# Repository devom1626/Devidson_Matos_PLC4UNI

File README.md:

# Devidson\_Matos\_PLC4UNI

CONSISTE EN EL "MAKING OF" DE UNA TARJETA TERMINADA DE PLC USANDO EL FAMOSO ESP32 COMO CEREBRO PRINCIPAL, APLICANDO FUNCIONES GENERALES DE UN PLC DE USO DEL DIA A DIA.

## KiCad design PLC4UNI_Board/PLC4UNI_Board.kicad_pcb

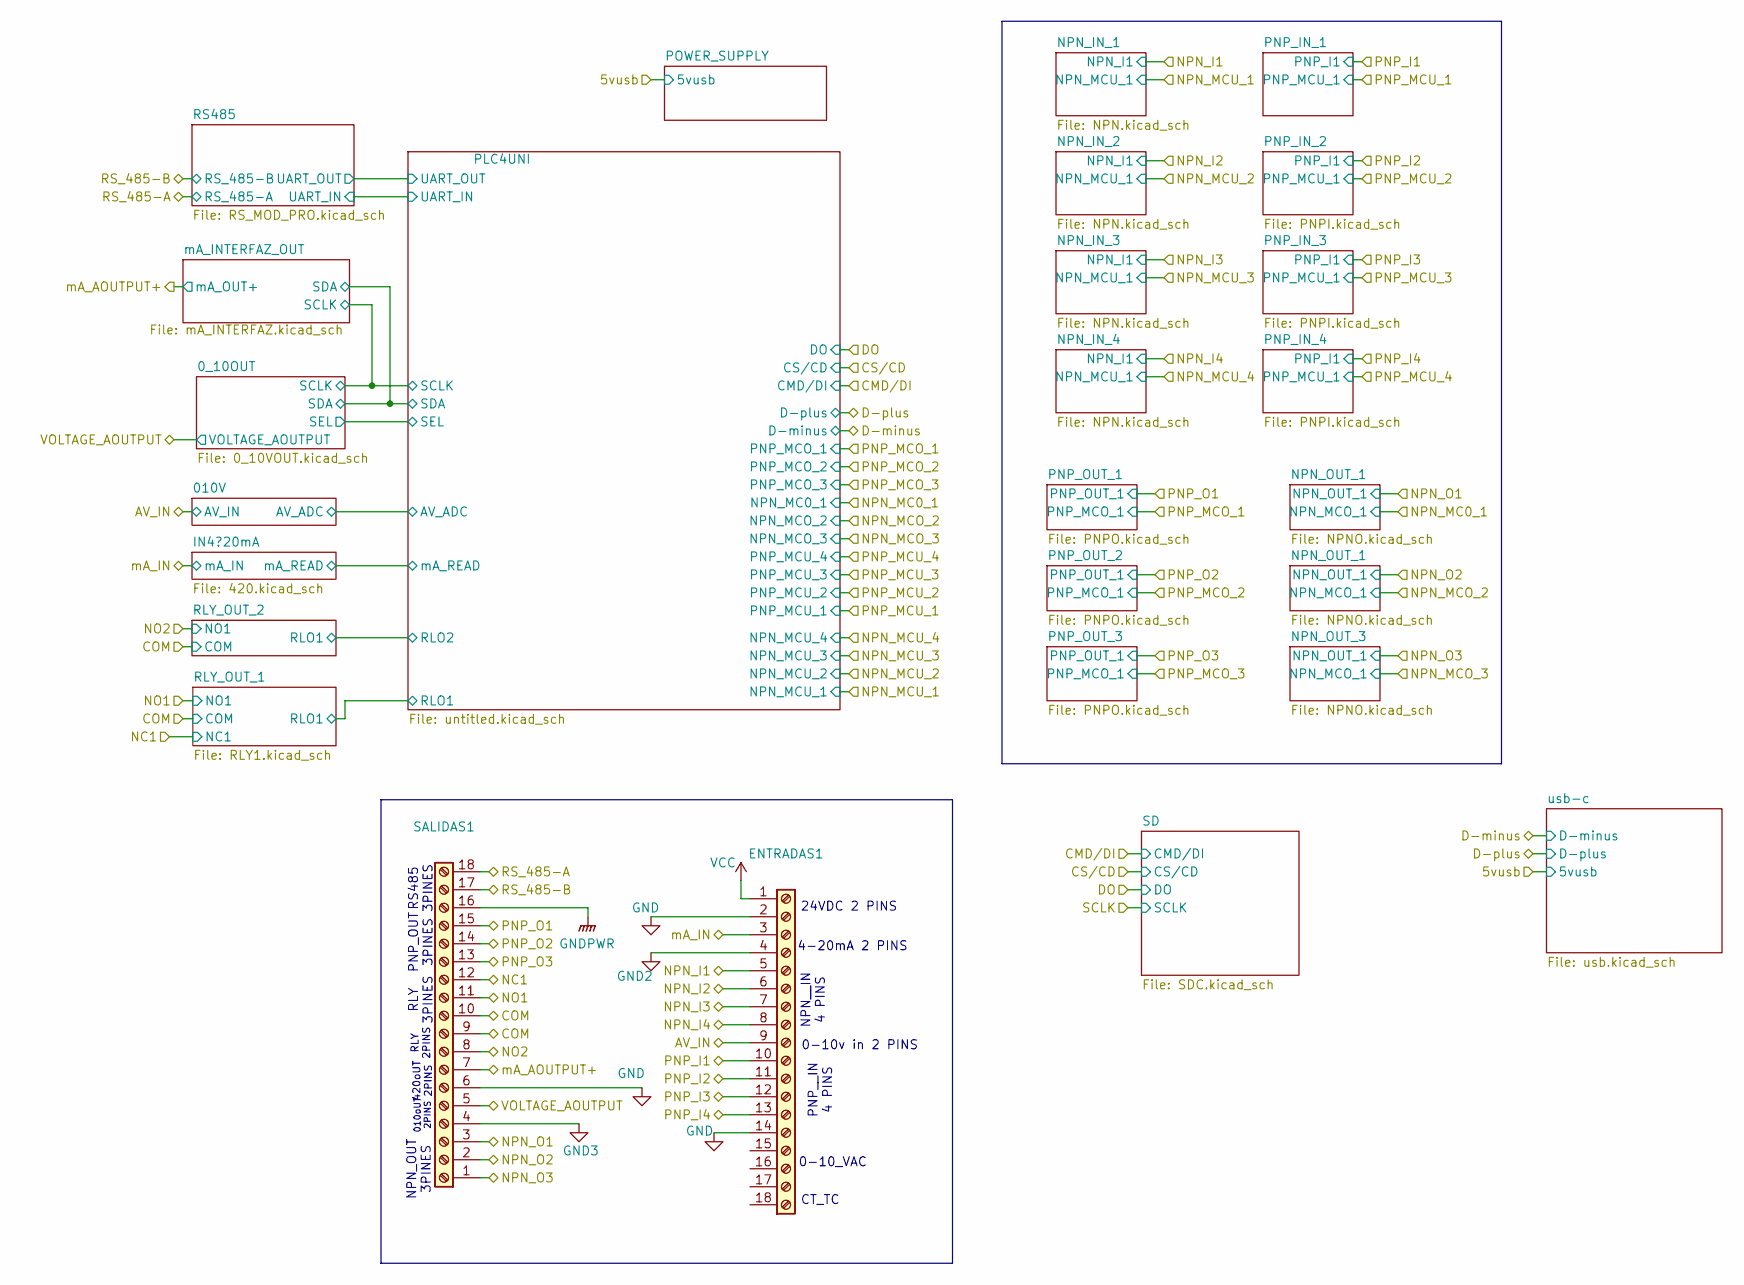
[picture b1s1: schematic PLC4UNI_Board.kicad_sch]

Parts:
ENTRADAS1: Screw_Terminal_01x18; TerminalBlock_MaiXu_MX126-5.0-18P_1x18_P5.00mm
SALIDAS1: Screw_Terminal_01x18; TerminalBlock_MaiXu_MX126-5.0-18P_1x18_P5.00mm

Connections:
/AV_IN: ENTRADAS1.9 (Pin_10); also elsewhere on the board
/COM: SALIDAS1.9, SALIDAS1.10; also elsewhere on the board
/NC1: SALIDAS1.12 (7); also elsewhere on the board
/NO1: SALIDAS1.11; also elsewhere on the board
/NO2: SALIDAS1.8; also elsewhere on the board
/NPN_I1: ENTRADAS1.5 (Pin_14); also elsewhere on the board
/NPN_I2: ENTRADAS1.6 (Pin_13); also elsewhere on the board
/NPN_I3: ENTRADAS1.7 (Pin_12); also elsewhere on the board
/NPN_I4: ENTRADAS1.8 (Pin_11); also elsewhere on the board
/NPN_O1: SALIDAS1.3; also elsewhere on the board
/NPN_O2: SALIDAS1.2; also elsewhere on the board
/NPN_O3: SALIDAS1.1; also elsewhere on the board
/PNP_I1: ENTRADAS1.10 (Pin_9); also elsewhere on the board
/PNP_I2: ENTRADAS1.11 (Pin_8); also elsewhere on the board
/PNP_I3: ENTRADAS1.12 (Pin_7); also elsewhere on the board
/PNP_I4: ENTRADAS1.13 (Pin_6); also elsewhere on the board
/PNP_O1: SALIDAS1.15; also elsewhere on the board
/PNP_O2: SALIDAS1.14; also elsewhere on the board
/PNP_O3: SALIDAS1.13; also elsewhere on the board
/RS_485-A: SALIDAS1.18; also elsewhere on the board
/RS_485-B: SALIDAS1.17; also elsewhere on the board
/VOLTAGE_AOUTPUT: SALIDAS1.5; also elsewhere on the board
/mA_AOUTPUT+: SALIDAS1.7; also elsewhere on the board
/mA_IN: ENTRADAS1.3 (Pin_16); also elsewhere on the board
GND: ENTRADAS1.2 (Pin_17), ENTRADAS1.14 (Pin_5), SALIDAS1.6; also elsewhere on the board
GND2: ENTRADAS1.4 (Pin_15); also elsewhere on the board
GND3: SALIDAS1.4; also elsewhere on the board
GNDPWR: SALIDAS1.16; also elsewhere on the board
VCC: ENTRADAS1.1 (Pin_18); also elsewhere on the board

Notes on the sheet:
4-20mA 2 PINS
0-10_VAC
NPN_OUT 3PINES
010oUT 2PINS
0-10v in 2 PINS
PNP_OUT 3PINES
CT_TC
PNP__IN 4 PINS
RS485 3PINES
NPN__IN 4 PINS
RLY 2PINS
RLY 3PINES
24VDC 2 PINS
420oUT 2PINS

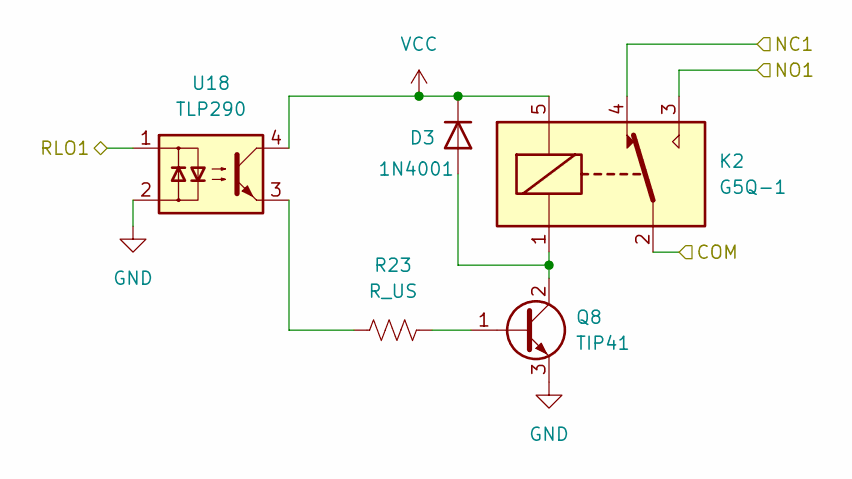
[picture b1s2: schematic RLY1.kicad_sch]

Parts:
D3: 1N4001; D_DO-41_SOD81_P10.16mm_Horizontal
K2: G5Q-1; Relay_SPDT_Omron-G5Q-1
Q8: TIP41; TO-252-2
R23: R_US; R_0201_0603Metric
U18: TLP290; SOP-4_4.4x2.6mm_P1.27mm

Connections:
/COM: K2.2; also elsewhere on the board
/NO2: K2.3; also elsewhere on the board
/PLC4UNI/RLO2: U18.1; also elsewhere on the board
/RLY_OUT_2/NC1: K2.4
GND: Q8.3 (E), U18.2; also elsewhere on the board
unnamed: D3.2 (A), K2.1, Q8.2 (C)
unnamed: Q8.1 (B), R23.2
unnamed: R23.1, U18.3
VCC: D3.1 (K), K2.5, U18.4; also elsewhere on the board

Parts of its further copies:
D1: 1N4001; D_DO-41_SOD81_P10.16mm_Horizontal
K1: G5Q-1; Relay_SPDT_Omron-G5Q-1
Q7: TIP41; TO-252-2
R22: R_US; R_0201_0603Metric
U17: TLP290; SOP-4_4.4x2.6mm_P1.27mm

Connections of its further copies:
/COM: K1.2; also elsewhere on the board
/NC1: K1.4; also elsewhere on the board
/NO1: K1.3; also elsewhere on the board
/PLC4UNI/RLO1: U17.1; also elsewhere on the board
GND: Q7.3 (E), U17.2; also elsewhere on the board
unnamed: D1.2 (A), K1.1, Q7.2 (C)
unnamed: Q7.1 (B), R22.2
unnamed: R22.1, U17.3
VCC: D1.1 (K), K1.5, U17.4; also elsewhere on the board

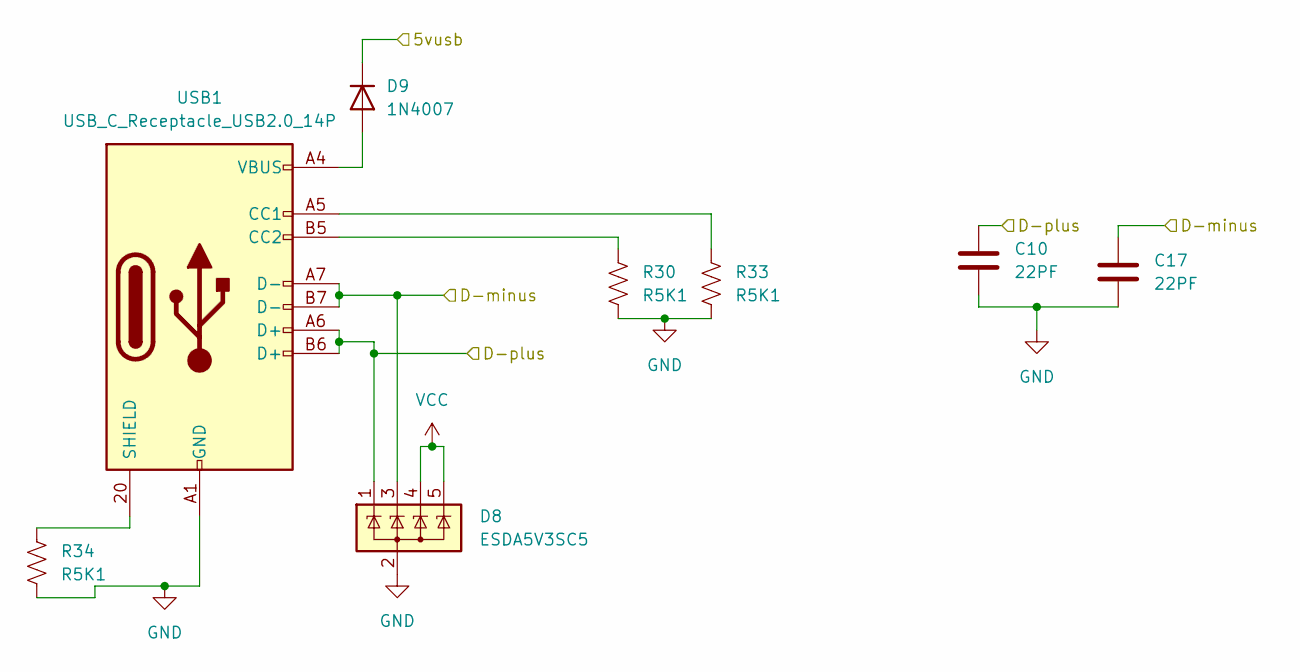
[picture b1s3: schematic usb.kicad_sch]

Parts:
C10, C17: 22PF; C_0603_1608Metric
D8: ESDA5V3SC5; SOT-23-5
D9: 1N4007; D_0603_1608Metric_Pad1.05x0.95mm_HandSolder
R30, R33, R34: R5K1; R_0201_0603Metric
USB1: USB_C_Receptacle_USB2.0_14P; USB-C-TH_HX-TYPE-C-16P-180-LC-BH10.0-TYPE-C-VERTICAL

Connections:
/5vusb: D9.1 (K); also elsewhere on the board
/D-minus: C17.1, D8.3 (K), USB1.A7 (D-), USB1.B7 (D-); also elsewhere on the board
/D-plus: C10.1, D8.1 (K), USB1.A6 (D+), USB1.B6 (D+); also elsewhere on the board
GND: C10.2, C17.2, D8.2 (A), R30.2, R33.2, R34.2, USB1.A1 (GND), USB1.A12 (GND), USB1.B1 (GND), USB1.B12 (GND); also elsewhere on the board
unnamed: D9.2 (A), USB1.A4 (VBUS), USB1.A9 (VBUS), USB1.B4 (VBUS), USB1.B9 (VBUS)
unnamed: R33.1, USB1.A5 (CC1)
unnamed: R30.1, USB1.B5 (CC2)
unnamed: R34.1, USB1.20 (SHIELD)
VCC: D8.4 (K), D8.5 (K); also elsewhere on the board

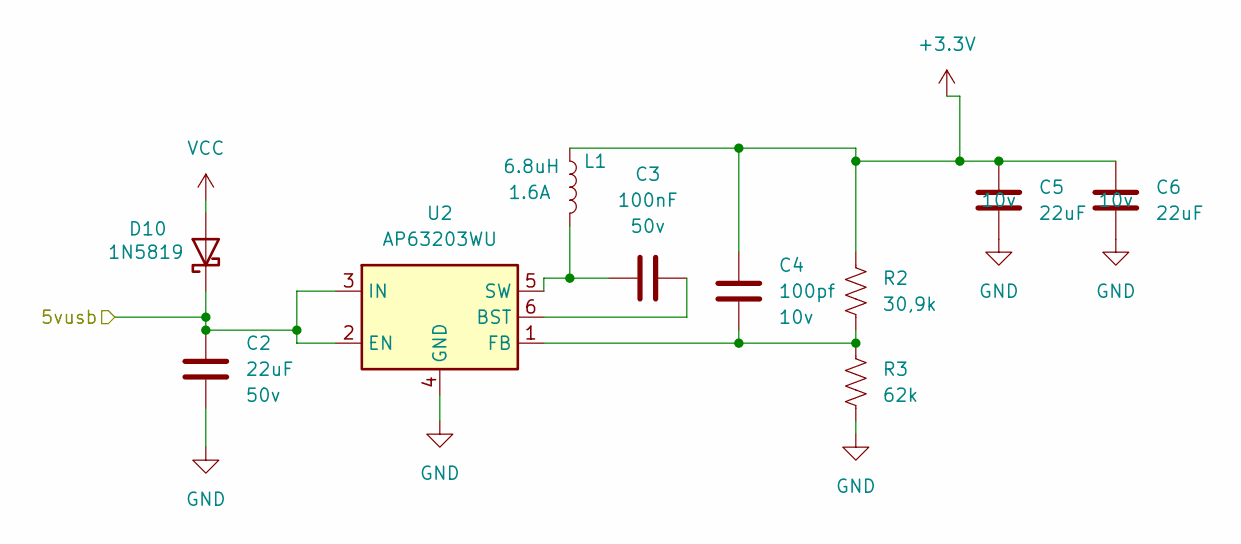
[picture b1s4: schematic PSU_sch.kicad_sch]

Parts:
C2: 22uF; C_1206_3216Metric
C3: 100nF; R_0805_2012Metric
C4: 100pf; R_0805_2012Metric
C5, C6: 22uF; C_0805_2012Metric_Pad1.18x1.45mm_HandSolder
D10: 1N5819; D_0603_1608Metric_Pad1.05x0.95mm_HandSolder
L1: 6.8uH_1.0A_4018; L_Changjiang_FNR5040S; Part Number NRS4018T6R8MDGJ; JLCPCB ID C223055
R2: 30,9k; R_0805_2012Metric
R3: 62k; R_0201_0603Metric
U2: AP63203WU; TSOT-23-6

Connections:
+3.3V: C4.1, C5.1, C6.1, L1.1, R2.1; also elsewhere on the board
/5vusb: C2.1, D10.1 (K), U2.2 (EN), U2.3 (IN); also elsewhere on the board
GND: C2.2, C5.2, C6.2, R3.2, U2.4 (GND); also elsewhere on the board
unnamed: C3.2, U2.6 (BST)
unnamed: C4.2, R2.2, R3.1, U2.1 (FB)
unnamed: C3.1, L1.2, U2.5 (SW)
VCC: D10.2 (A); also elsewhere on the board

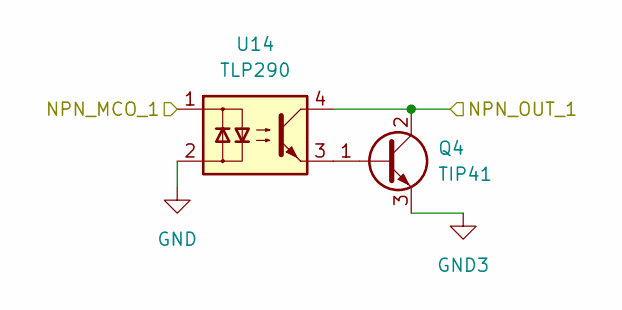
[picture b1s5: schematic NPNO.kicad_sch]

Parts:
Q4: TIP41; TO-252-2
U14: TLP290; SOP-4_4.4x2.6mm_P1.27mm

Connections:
/NPN_MCO_2: U14.1; also elsewhere on the board
/NPN_O2: Q4.2 (C), U14.4; also elsewhere on the board
GND: U14.2; also elsewhere on the board
GND3: Q4.3 (E); also elsewhere on the board
unnamed: Q4.1 (B), U14.3

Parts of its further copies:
Q5, Q6: TIP41; TO-252-2
U15, U16: TLP290; SOP-4_4.4x2.6mm_P1.27mm

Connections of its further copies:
/NPN_MC0_1: U16.1; also elsewhere on the board
/NPN_MCO_3: U15.1; also elsewhere on the board
/NPN_O1: Q6.2 (C), U16.4; also elsewhere on the board
/NPN_O3: Q5.2 (C), U15.4; also elsewhere on the board
GND: U15.2, U16.2; also elsewhere on the board
GND3: Q5.3 (E), Q6.3 (E); also elsewhere on the board
unnamed: Q5.1 (B), U15.3
unnamed: Q6.1 (B), U16.3

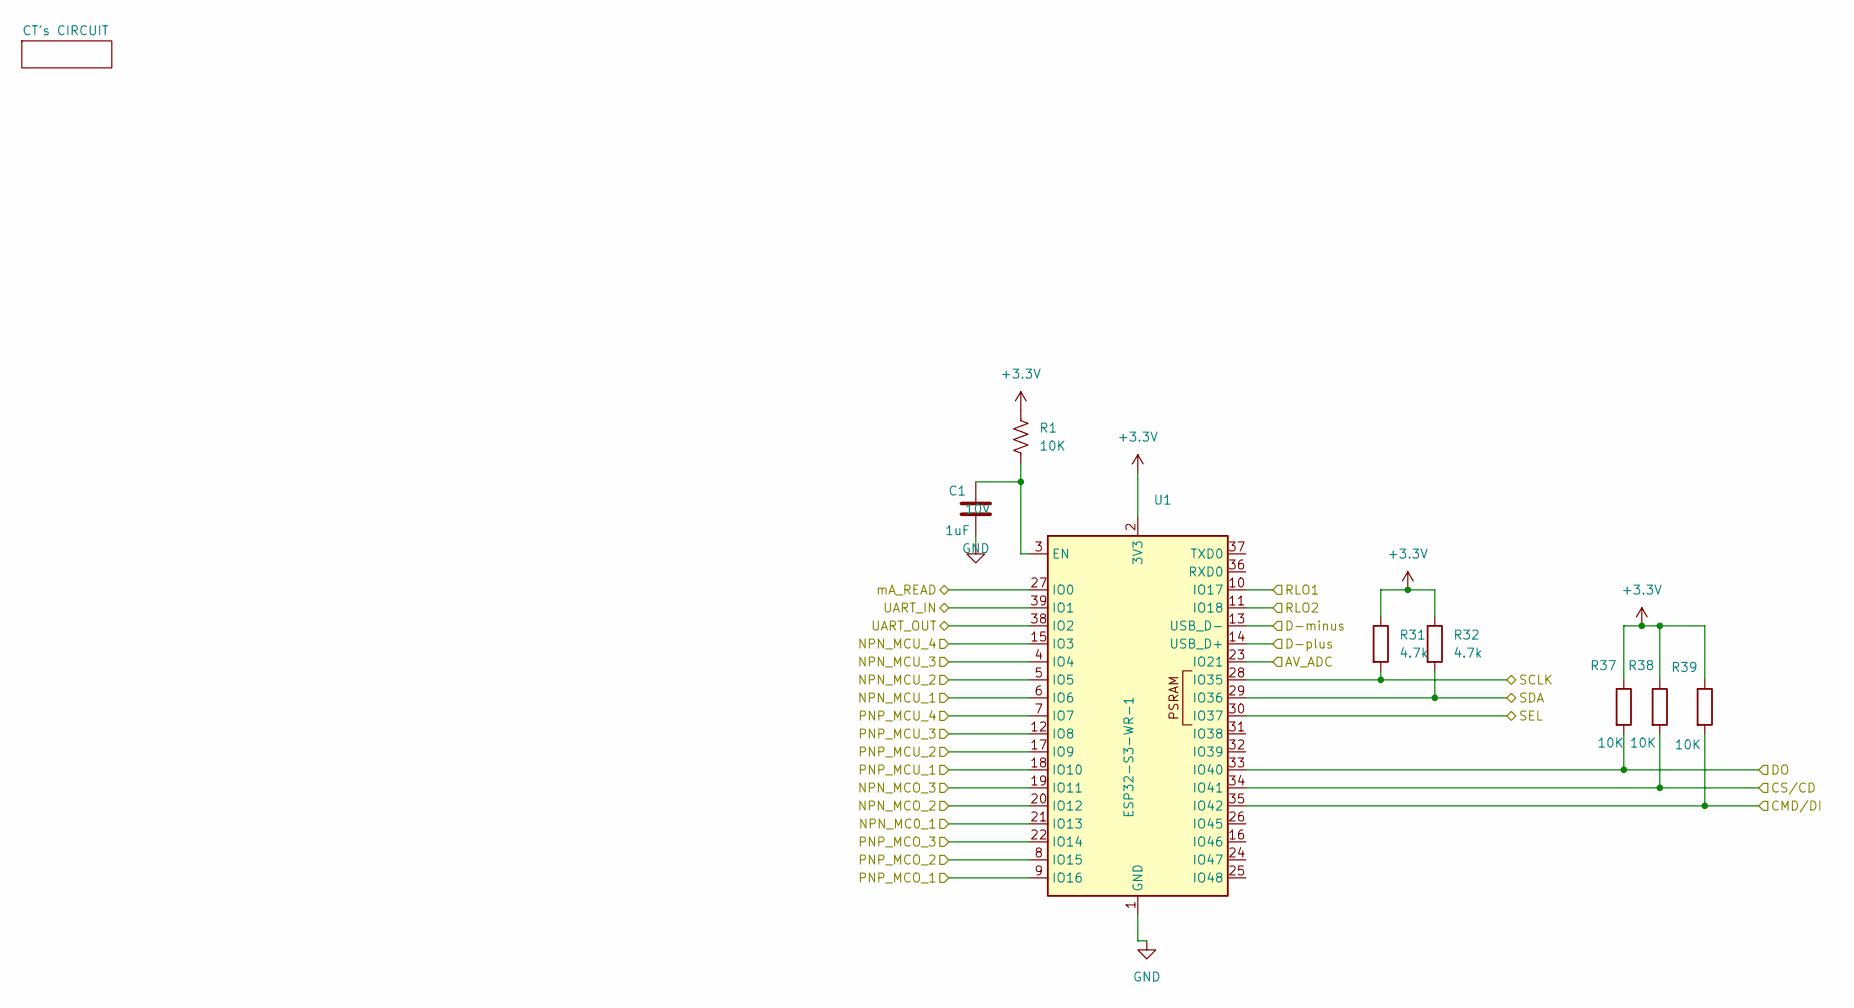
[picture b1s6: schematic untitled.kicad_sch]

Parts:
C1: 1uF; C_1206_3216Metric_Pad1.33x1.80mm_HandSolder
R1: 10K; R_0201_0603Metric
R31, R32: 4.7k; R_0603_1608Metric
R37, R38, R39: 10K; R_0603_1608Metric
U1: ESP32-S3-WR-1; ESP32-S3-WROOM-1

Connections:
+3.3V: R1.1, R31.1, R32.1, R37.1, R38.1, R39.1, U1.2 (3V3); also elsewhere on the board
/0_10OUT/SCLK: R31.2, U1.28 (IO35); also elsewhere on the board
/0_10OUT/SDA: R32.2, U1.29 (IO36); also elsewhere on the board
/0_10OUT/SEL: U1.30 (IO37); also elsewhere on the board
/010V/AV_ADC: U1.23 (IO21); also elsewhere on the board
/CMD/DI: R39.2, U1.35 (IO42); also elsewhere on the board
/CS/CD: R38.2, U1.34 (IO41); also elsewhere on the board
/D-minus: U1.13 (USB_D-); also elsewhere on the board
/D-plus: U1.14 (USB_D+); also elsewhere on the board
/DO: R37.2, U1.33 (IO40); also elsewhere on the board
/NPN_MC0_1: U1.21 (IO13); also elsewhere on the board
/NPN_MCO_2: U1.20 (IO12); also elsewhere on the board
/NPN_MCO_3: U1.19 (IO11); also elsewhere on the board
/NPN_MCU_1: U1.6 (IO6); also elsewhere on the board
/NPN_MCU_2: U1.5 (IO5); also elsewhere on the board
/NPN_MCU_3: U1.4 (IO4); also elsewhere on the board
/NPN_MCU_4: U1.15 (IO3); also elsewhere on the board
/PLC4UNI/RLO1: U1.10 (IO17); also elsewhere on the board
/PLC4UNI/RLO2: U1.11 (IO18); also elsewhere on the board
/PLC4UNI/UART_IN: U1.39 (IO1); also elsewhere on the board
/PLC4UNI/UART_OUT: U1.38 (IO2); also elsewhere on the board
/PNP_MCO_1: U1.9 (IO16); also elsewhere on the board
/PNP_MCO_2: U1.8 (IO15); also elsewhere on the board
/PNP_MCO_3: U1.22 (IO14); also elsewhere on the board
/PNP_MCU_1: U1.18 (IO10); also elsewhere on the board
/PNP_MCU_2: U1.17 (IO9); also elsewhere on the board
/PNP_MCU_3: U1.12 (IO8); also elsewhere on the board
/PNP_MCU_4: U1.7 (IO7); also elsewhere on the board
/mA_IN: U1.27 (IO0); also elsewhere on the board
GND: C1.2, U1.1 (GND), U1.40 (GND), U1.41 (GND); also elsewhere on the board
unnamed: C1.1, R1.2, U1.3 (EN)

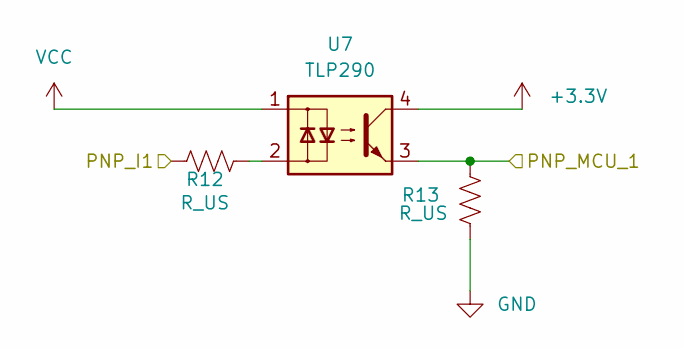
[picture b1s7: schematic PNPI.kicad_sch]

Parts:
R12: R_US; R_0603_1608Metric
R13: R_US; R_0201_0603Metric
U7: TLP290; SOP-4_4.4x2.6mm_P1.27mm

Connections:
+3.3V: U7.4; also elsewhere on the board
/PNP_I1: R12.1; also elsewhere on the board
/PNP_MCU_1: R13.1, U7.3; also elsewhere on the board
GND: R13.2; also elsewhere on the board
unnamed: R12.2, U7.2
VCC: U7.1; also elsewhere on the board

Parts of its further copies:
R14, R16, R18: R_US; R_0603_1608Metric
R15, R17, R19: R_US; R_0201_0603Metric
U8, U9, U10: TLP290; SOP-4_4.4x2.6mm_P1.27mm

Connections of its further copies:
+3.3V: U8.4, U9.4, U10.4; also elsewhere on the board
/PNP_I2: R14.1; also elsewhere on the board
/PNP_I3: R16.1; also elsewhere on the board
/PNP_I4: R18.1; also elsewhere on the board
/PNP_MCU_2: R15.1, U8.3; also elsewhere on the board
/PNP_MCU_3: R17.1, U9.3; also elsewhere on the board
/PNP_MCU_4: R19.1, U10.3; also elsewhere on the board
GND: R15.2, R17.2, R19.2; also elsewhere on the board
unnamed: R14.2, U8.2
unnamed: R16.2, U9.2
unnamed: R18.2, U10.2
VCC: U8.1, U9.1, U10.1; also elsewhere on the board

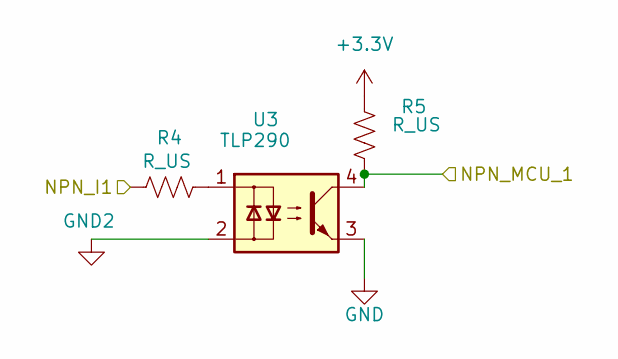
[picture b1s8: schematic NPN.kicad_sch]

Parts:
R4, R5: R_US; R_0201_0603Metric
U3: TLP290; SOP-4_4.4x2.6mm_P1.27mm

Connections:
+3.3V: R5.1; also elsewhere on the board
/NPN_I1: R4.1; also elsewhere on the board
/NPN_MCU_1: R5.2, U3.4; also elsewhere on the board
GND: U3.3; also elsewhere on the board
GND2: U3.2; also elsewhere on the board
unnamed: R4.2, U3.1

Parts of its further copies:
R6, R7, R8, R9, R10, R11: R_US; R_0201_0603Metric
U4, U5, U6: TLP290; SOP-4_4.4x2.6mm_P1.27mm

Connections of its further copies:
+3.3V: R7.1, R9.1, R11.1; also elsewhere on the board
/NPN_I2: R6.1; also elsewhere on the board
/NPN_I3: R8.1; also elsewhere on the board
/NPN_I4: R10.1; also elsewhere on the board
/NPN_MCU_2: R7.2, U4.4; also elsewhere on the board
/NPN_MCU_3: R9.2, U5.4; also elsewhere on the board
/NPN_MCU_4: R11.2, U6.4; also elsewhere on the board
GND: U4.3, U5.3, U6.3; also elsewhere on the board
GND2: U4.2, U5.2, U6.2; also elsewhere on the board
unnamed: R6.2, U4.1
unnamed: R8.2, U5.1
unnamed: R10.2, U6.1

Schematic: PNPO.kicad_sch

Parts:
Q9: TIP42; TO-252-2
U11: TLP290; SOP-4_4.4x2.6mm_P1.27mm

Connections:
/PNP_MCO_2: U11.1; also elsewhere on the board
/PNP_O2: Q9.2 (C), U11.4; also elsewhere on the board
GND: U11.2; also elsewhere on the board
unnamed: Q9.1 (B), U11.3
VCC: Q9.3 (E); also elsewhere on the board

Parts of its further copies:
Q10, Q11: TIP42; TO-252-2
U12, U13: TLP290; SOP-4_4.4x2.6mm_P1.27mm

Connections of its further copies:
/PNP_MCO_1: U13.1; also elsewhere on the board
/PNP_MCO_3: U12.1; also elsewhere on the board
/PNP_O1: Q11.2 (C), U13.4; also elsewhere on the board
/PNP_O3: Q10.2 (C), U12.4; also elsewhere on the board
GND: U12.2, U13.2; also elsewhere on the board
unnamed: Q10.1 (B), U12.3
unnamed: Q11.1 (B), U13.3
VCC: Q10.3 (E), Q11.3 (E); also elsewhere on the board

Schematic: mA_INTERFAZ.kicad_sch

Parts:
C12: 220pF; C_0805_2012Metric
C13, C14: 1uF; C_0805_2012Metric
C15: 100nF; C_0805_2012Metric
D2: D_Zener; D_0603_1608Metric
D6: SMF24A; D_SMF
D7: 1N4007; D_0603_1608Metric_Pad1.05x0.95mm_HandSolder
JP1, JP2, JP3: SolderJumper_2_Open; SolderJumper-2_P1.3mm_Open_TrianglePad1.0x1.5mm
R26, R29, R35: 10k; R_0201_0603Metric
R27: 100k; R_0201_0603Metric
R28: 15; R_0201_0603Metric
RAI1: 2.5k; R_0201_0603Metric
T1: IRF9310TRPBF; SOIC-8_5.3x5.3mm_P1.27mm
U20: SSOP-10-1EP_3.9x4.9mm_P1mm_EP2.1x3.3mm

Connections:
/0_10OUT/SCLK: U20.1 (SCLK); also elsewhere on the board
/0_10OUT/SDA: U20.2 (SDA); also elsewhere on the board
/mA_AOUTPUT+: D7.1 (K); also elsewhere on the board
GND: C12.2, C13.2, C14.2, C15.2, D6.2 (A2), JP1.1 (A), JP2.1 (A), JP3.1 (A), R27.2, RAI1.2, U20.6 (GND); also elsewhere on the board
unnamed: C14.1, D2.2 (A), R27.1, T1.4
unnamed: C15.1, D6.1 (A1), R28.1, T1.5, T1.6, T1.7, T1.8
unnamed: D7.2 (A), R28.2
unnamed: JP1.2 (B), R29.2, U20.4 (A1)
unnamed: JP2.2 (B), R26.2, U20.3 (A0)
unnamed: JP3.2 (B), R35.2, U20.9 (A2)
unnamed: T1.1, T1.2, T1.3, U20.8 (IOUT)
unnamed: C12.1, RAI1.1, U20.7 (SET)
unnamed: C13.1, R26.1, R29.1, R35.1, U20.10 (V5V)
VCC: D2.1 (K), U20.5 (VCC); also elsewhere on the board

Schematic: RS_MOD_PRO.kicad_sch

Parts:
J4: Conn_01x03; PinHeader_1x03_P2.54mm_Vertical
U21: Untitled

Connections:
+3.3V: U21.1 (VCC); also elsewhere on the board
/PLC4UNI/UART_IN: U21.4 (´RX); also elsewhere on the board
/PLC4UNI/UART_OUT: U21.3 (TX); also elsewhere on the board
/RS_485-A: J4.9 (Pin_2), U21.9 (A); also elsewhere on the board
/RS_485-B: J4.8 (Pin_1), U21.8 (B); also elsewhere on the board
GND: U21.2 (GND); also elsewhere on the board
GNDPWR: J4.10 (Pin_3), U21.10 (RGND); also elsewhere on the board

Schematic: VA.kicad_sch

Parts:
C9: 100nF; C_0805_2012Metric_Pad1.18x1.45mm_HandSolder
D4: PTVS10VZ1USK; Nexperia_DSN1608-2_1.6x0.8mm
R21: 22K; R_0603_1608Metric
R24: 10K; R_0603_1608Metric

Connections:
/010V/AV_ADC: C9.1, D4.1 (K), R21.2, R24.1; also elsewhere on the board
/AV_IN: R21.1; also elsewhere on the board
GND: C9.2, D4.2 (A), R24.2; also elsewhere on the board

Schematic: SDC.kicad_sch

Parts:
USB2: USB_C_Receptacle_USB2.0_14P; USB-C-TH_HX-TYPE-C-16P-180-LC-BH10.0-TYPE-C-VERTICAL

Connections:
unnamed: USB2.A1 (GND), USB2.A12 (GND), USB2.B1 (GND), USB2.B12 (GND)
unnamed: USB2.A4 (VBUS), USB2.A9 (VBUS), USB2.B4 (VBUS), USB2.B9 (VBUS)

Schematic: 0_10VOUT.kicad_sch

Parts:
C7: 1uF; C_0805_2012Metric_Pad1.18x1.45mm_HandSolder
C8: 100nF; C_0805_2012Metric
D5: SMF24A; D_SMF; LCSC# C7495269
R25: 10k; R_0603_1608Metric
U19: SOIC-8_5.3x5.3mm_P1.27mm

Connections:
/0_10OUT/SCLK: U19.1 (SCLK); also elsewhere on the board
/0_10OUT/SDA: U19.2 (SDA); also elsewhere on the board
/0_10OUT/SEL: R25.1, U19.7 (SEL); also elsewhere on the board
/VOLTAGE_AOUTPUT: C8.2, D5.1 (A1), U19.6 (VOUT); also elsewhere on the board
GND: C7.1, C8.1, D5.2 (A2), U19.5 (GND); also elsewhere on the board
unnamed: C7.2, R25.2, U19.8 (V5V)
VCC: U19.4 (VCC); also elsewhere on the board

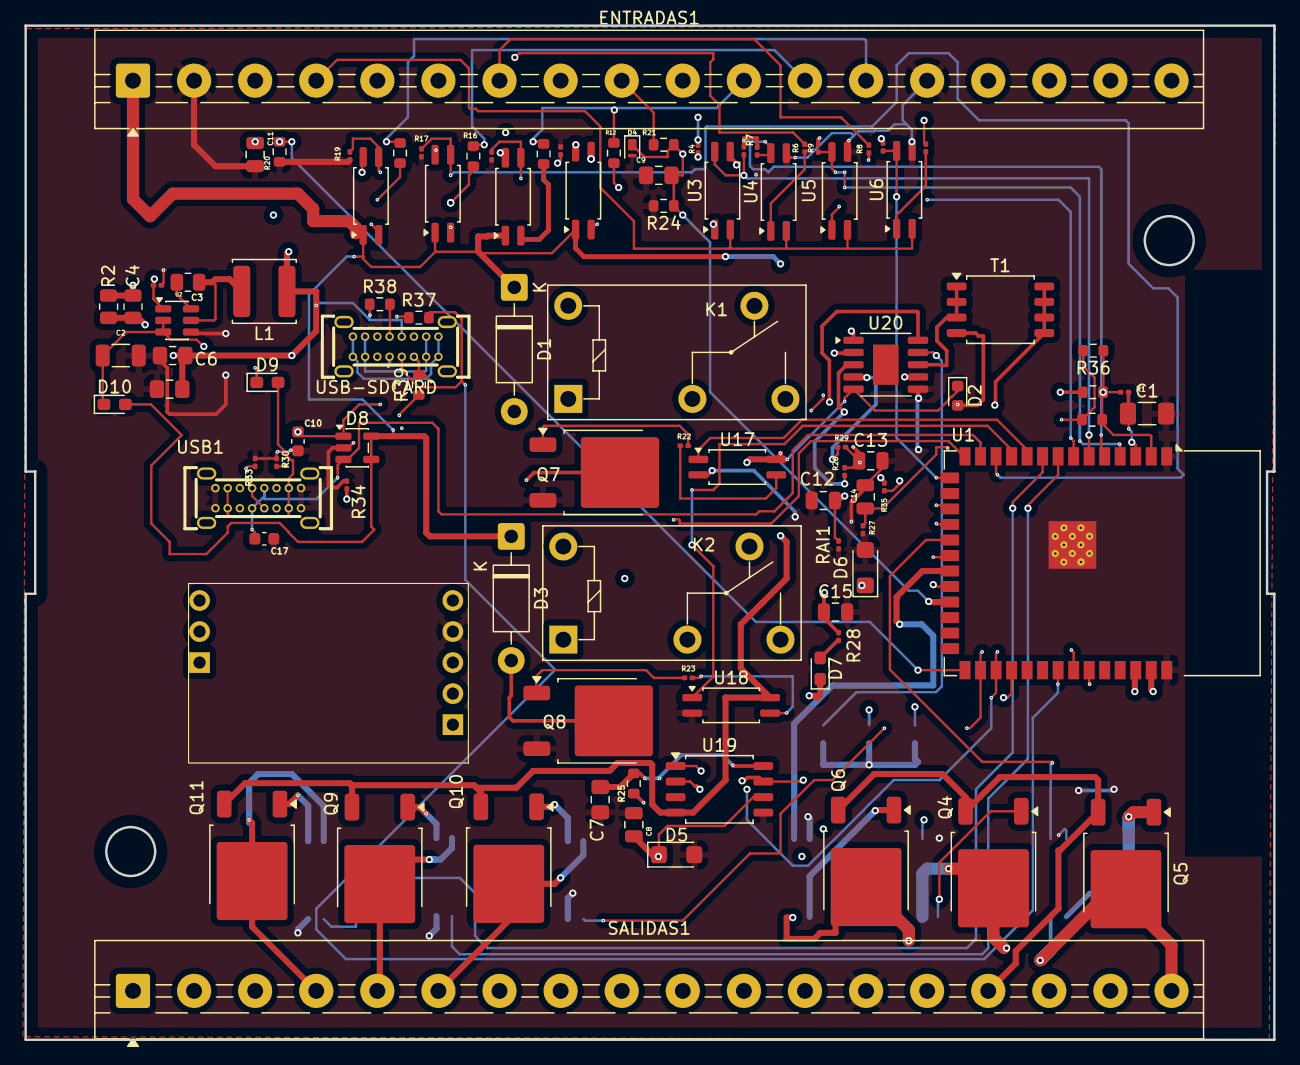
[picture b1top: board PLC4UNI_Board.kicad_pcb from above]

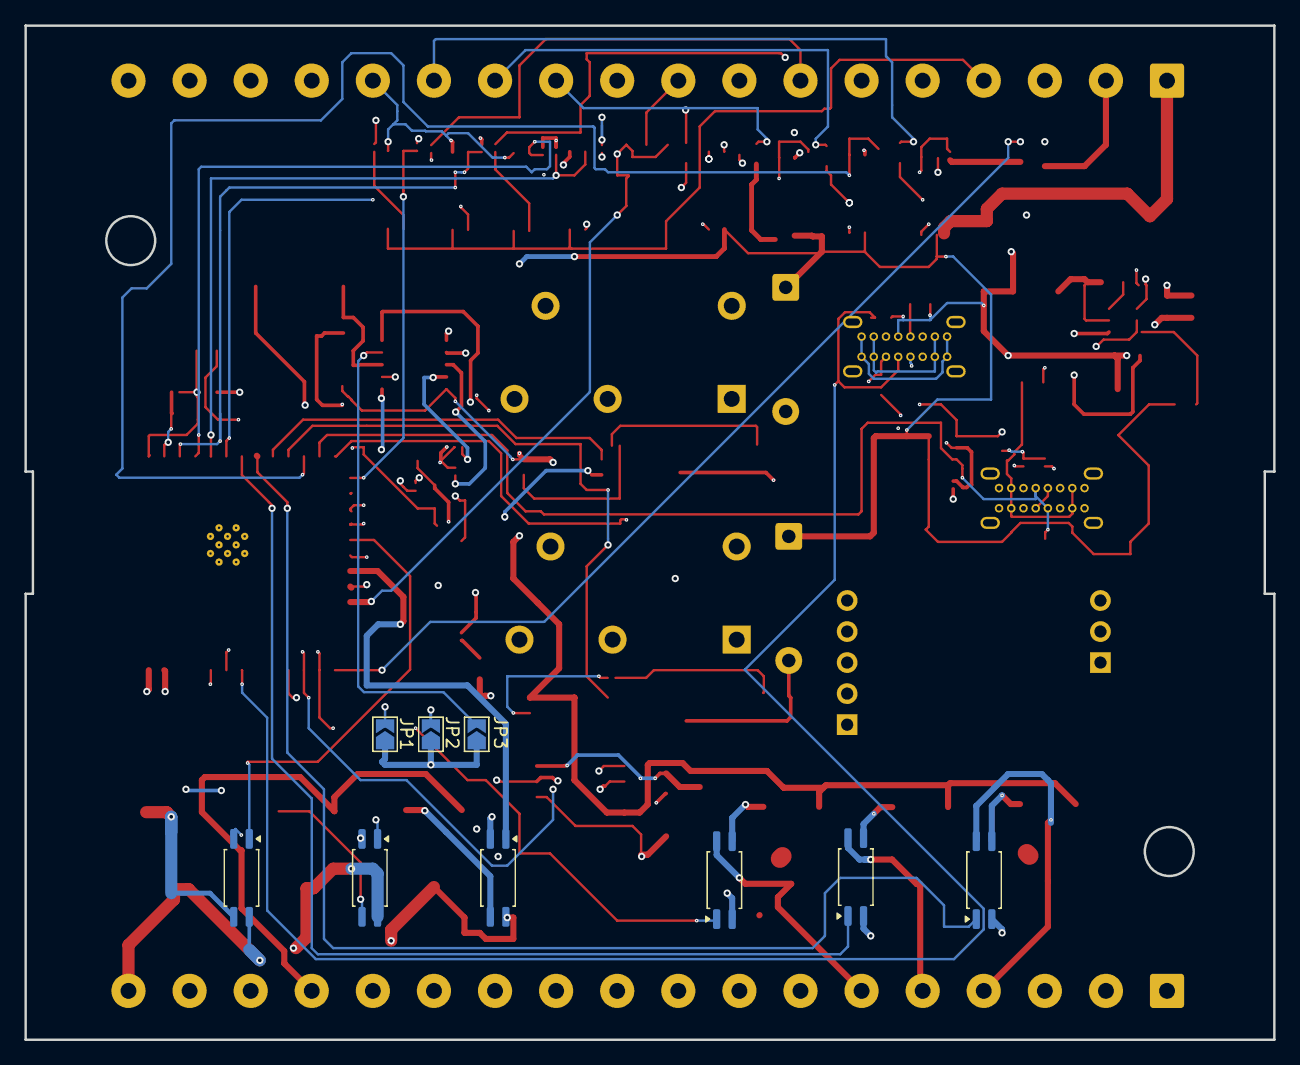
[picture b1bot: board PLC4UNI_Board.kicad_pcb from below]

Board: 4 copper layers, 102.2 x 83.0 mm, 106 parts (9 on the bottom side), 98 nets.

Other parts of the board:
C11: 100nF; C_0805_2012Metric
R20: 120; R_0603_1608Metric
R36: 10K; R_0603_1608Metric
USB-SDCARD: USB_C_Receptacle_USB2.0_14P; USB-C-TH_HX-TYPE-C-16P-180-LC-BH10.0-TYPE-C-VERTICAL

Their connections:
+3.3V: R36.1, USB-SDCARD.A7 (D-); also elsewhere on the board
/0_10OUT/SCLK: R36.2; also elsewhere on the board
/CMD/DI: USB-SDCARD.B5 (CC2); also elsewhere on the board
/CS/CD: USB-SDCARD.A6 (D+); also elsewhere on the board
/DO: USB-SDCARD.B6 (D+); also elsewhere on the board
/mA_IN: C11.1, R20.2; also elsewhere on the board
GND: C11.2, R20.1, USB-SDCARD.B7 (D-); also elsewhere on the board
unnamed: USB-SDCARD.A1 (GND), USB-SDCARD.A12 (GND), USB-SDCARD.B1 (GND), USB-SDCARD.B12 (GND)
unnamed: USB-SDCARD.A4 (VBUS), USB-SDCARD.A9 (VBUS), USB-SDCARD.B4 (VBUS), USB-SDCARD.B9 (VBUS)

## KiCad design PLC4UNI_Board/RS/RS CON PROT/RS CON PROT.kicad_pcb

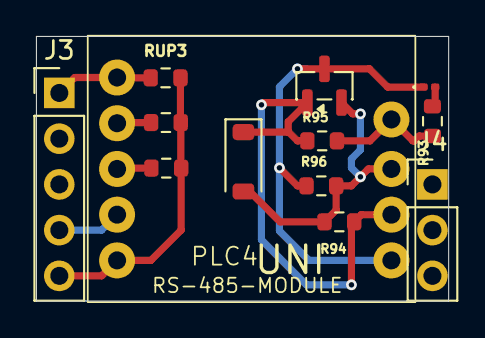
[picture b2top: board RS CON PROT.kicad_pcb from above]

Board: 4 copper layers, 22.9 x 14.7 mm, 13 parts (0 on the bottom side), 10 nets.

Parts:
D712: SM712_SOT23; SOT-23
DL1: LED; LED_0201_0603Metric
DTV1: D_TVS; D_SOD-123
J3: Conn_01x05; PinHeader_1x05_P2.54mm_Vertical
J4: Conn_01x03; PinHeader_1x03_P2.54mm_Vertical
R93, R94, R95, R96: R_US; R_0603_1608Metric
RUP1, RUP2, RUP3: R_US; R_0603_1608Metric
U0: RS485-MODULE-DEVO NU

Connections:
+3.3V: J3.1, RUP1.1, RUP2.1, RUP3.1, U0.1 (VCC)
/RS_mod_pro/RS_485-A: D712.1 (A1), DTV1.1 (A1), J4.9 (Pin_2), R94.2, R95.2, U0.9 (A)
/RS_mod_pro/RS_485-B: D712.2 (A2), DTV1.2 (A2), J4.8 (Pin_1), R94.1, R96.2, U0.8 (B)
/RS_mod_pro/UART_IN: J3.4, RUP2.2, U0.4 (RX)
/RS_mod_pro/UART_OUT: J3.3, RUP1.2, U0.3 (TX)
Earth: J3.2, U0.2 (GND)
unnamed: D712.3 (common), DL1.1 (K), J4.10 (Pin_3), R96.1, U0.10 (RGND)
unnamed: DL1.2 (A), R93.2
unnamed: J3.5, RUP3.2, U0.5 (CON)
unnamed: R93.1, R95.1, U0.7 (VO)

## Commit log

2025-09-27 main
2025-09-29 resubida de actualizaciones
2025-10-13 version
2025-10-17 v.1.0.1
2025-10-17 v1.0.1
2025-10-22 EDITION 1.0.2
2025-10-22 V1.0.2 PLC4UNI
2025-11-02 hola
2025-11-02 eliminar
2025-11-02 mod?dxf
2025-11-02 dxf_mod
2025-11-03 v2.1.0
2025-11-07 rs.v.2
2025-11-12 v.3.0.0
